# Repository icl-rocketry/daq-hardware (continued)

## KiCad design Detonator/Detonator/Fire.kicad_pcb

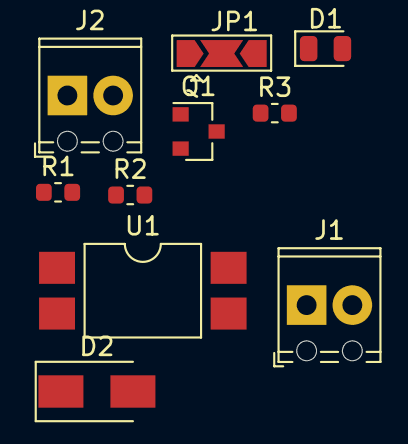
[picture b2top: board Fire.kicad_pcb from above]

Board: 2 copper layers, 10 parts (0 on the bottom side), 9 nets, no tracks yet.

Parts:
D1: FIRING; LED_0805_2012Metric
D2: DIODE; D_SMA
J1, J2: Screw_Terminal_01x02; TerminalBlock_Phoenix_MPT-0,5-2-2.54_1x02_P2.54mm_Horizontal
JP1: SolderJumper_3_Open; SolderJumper-3_P2.0mm_Open_TrianglePad1.0x1.5mm
Q1: DMN65D8L; SOT-23
R1: 1k; R_0603_1608Metric
R2, R3: 500; R_0603_1608Metric
U1: LTV-817S; SMDIP-4_W9.53mm

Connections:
+3V3: JP1.3, U1.1
/CONT: R2.1, U1.2
GND: J1.2, Q1.3, R2.2, R3.2
unnamed: D1.1, R1.1
unnamed: D1.2, J2.1, JP1.2
unnamed: D2.1, J2.2, U1.4
unnamed: D2.2, Q1.1, R1.2
unnamed: J1.1, JP1.1
unnamed: R3.1, U1.3

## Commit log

2019-10-05 Fixed folder structure
2019-10-17 Added initial schematic
2019-10-19 Created amps sheet
2019-10-19 Added thermocouples and amps sheet
2019-10-19 added reset and boot switches and barometer
2019-10-19 Thermocouples
    Added heirarchial sheet for thermocouples and the schematics
2019-10-19 Amplifier
    Added initial amplifier file amps.sch
2019-10-19 Amplifier
2019-10-19 amplifier changes
2019-10-19 made ads1219 symbol
2019-10-19 added analog input pins to main file
2019-10-19 Thermocouples
    Added components to the PCB. Please check the GND and VCC lines arrangement for any changes.
2019-10-19 amps uodate
2019-10-19 Power supply implementation
2019-10-20 Fixed Main schem and removed baro
2019-10-21 Auto stash before merge of "master" and "origin/master"
2019-10-22 Moved to iclr-hw library
2019-10-22 Removed extraneous project files
2019-10-22 Added gitignore
2019-10-22 Fixed gitignored files
2019-10-22 added analog inputs to daq-hardware
2019-10-22 changed adc's resistance to 4k7
2019-10-25 Changed SD card from SPI to SDIO
2019-10-25 Removed extraneous project file
2019-10-25 Amended boot pin, moved i2c pullups to main schematic
2019-10-25 Added necessary SDIO pullups
2019-10-25 Preliminary pin mapping and amended thermocouple hierarchical sheets
2019-10-25 Added and locked mounting holes
2019-10-25 Added indicator LEDs
2019-10-26 Pyros
2019-10-26 Added 12v and 5v power supply
2019-10-26 Layout for Pyros
2019-10-26 Via Shielding
2019-10-26 Added 5v and 12v power supply
2019-10-29 made the ads131m04 connections
2019-10-29 changed the hierarchical pins of the analogue
2019-10-29 added inductors footprint
2019-10-30 Not sure if this is gonna overwrite stuff but I try to push this anyway
2019-10-30 Fixed conflicts, assigned all footprints.
2019-10-30 Cleaned up layout, added barrel jack for power input
2019-10-30 Laid out +3V3 section
2019-10-31 Added 3D models, added ptaps sheet, fixed pyros
2019-10-31 Minor PCB rerouting
2019-11-02 layout changes
2019-11-05 Add Copper
2019-11-12 Release candidate
2019-11-12 Edward appeasement
2019-11-24 added BOM
    still not done
2019-11-30 slave testing
2019-11-30 slave+master
2019-12-03 new slave+master
    (i think it actually worked)
2019-12-03 the slave+master that works
    (sorry i dont know github i cant properly commit stuff)
2019-12-03 slave+master
    please be right
2019-12-03 slave+master (please work version)
2019-12-03 slave+master
    i'm struggling
2019-12-09 Updated BOM
